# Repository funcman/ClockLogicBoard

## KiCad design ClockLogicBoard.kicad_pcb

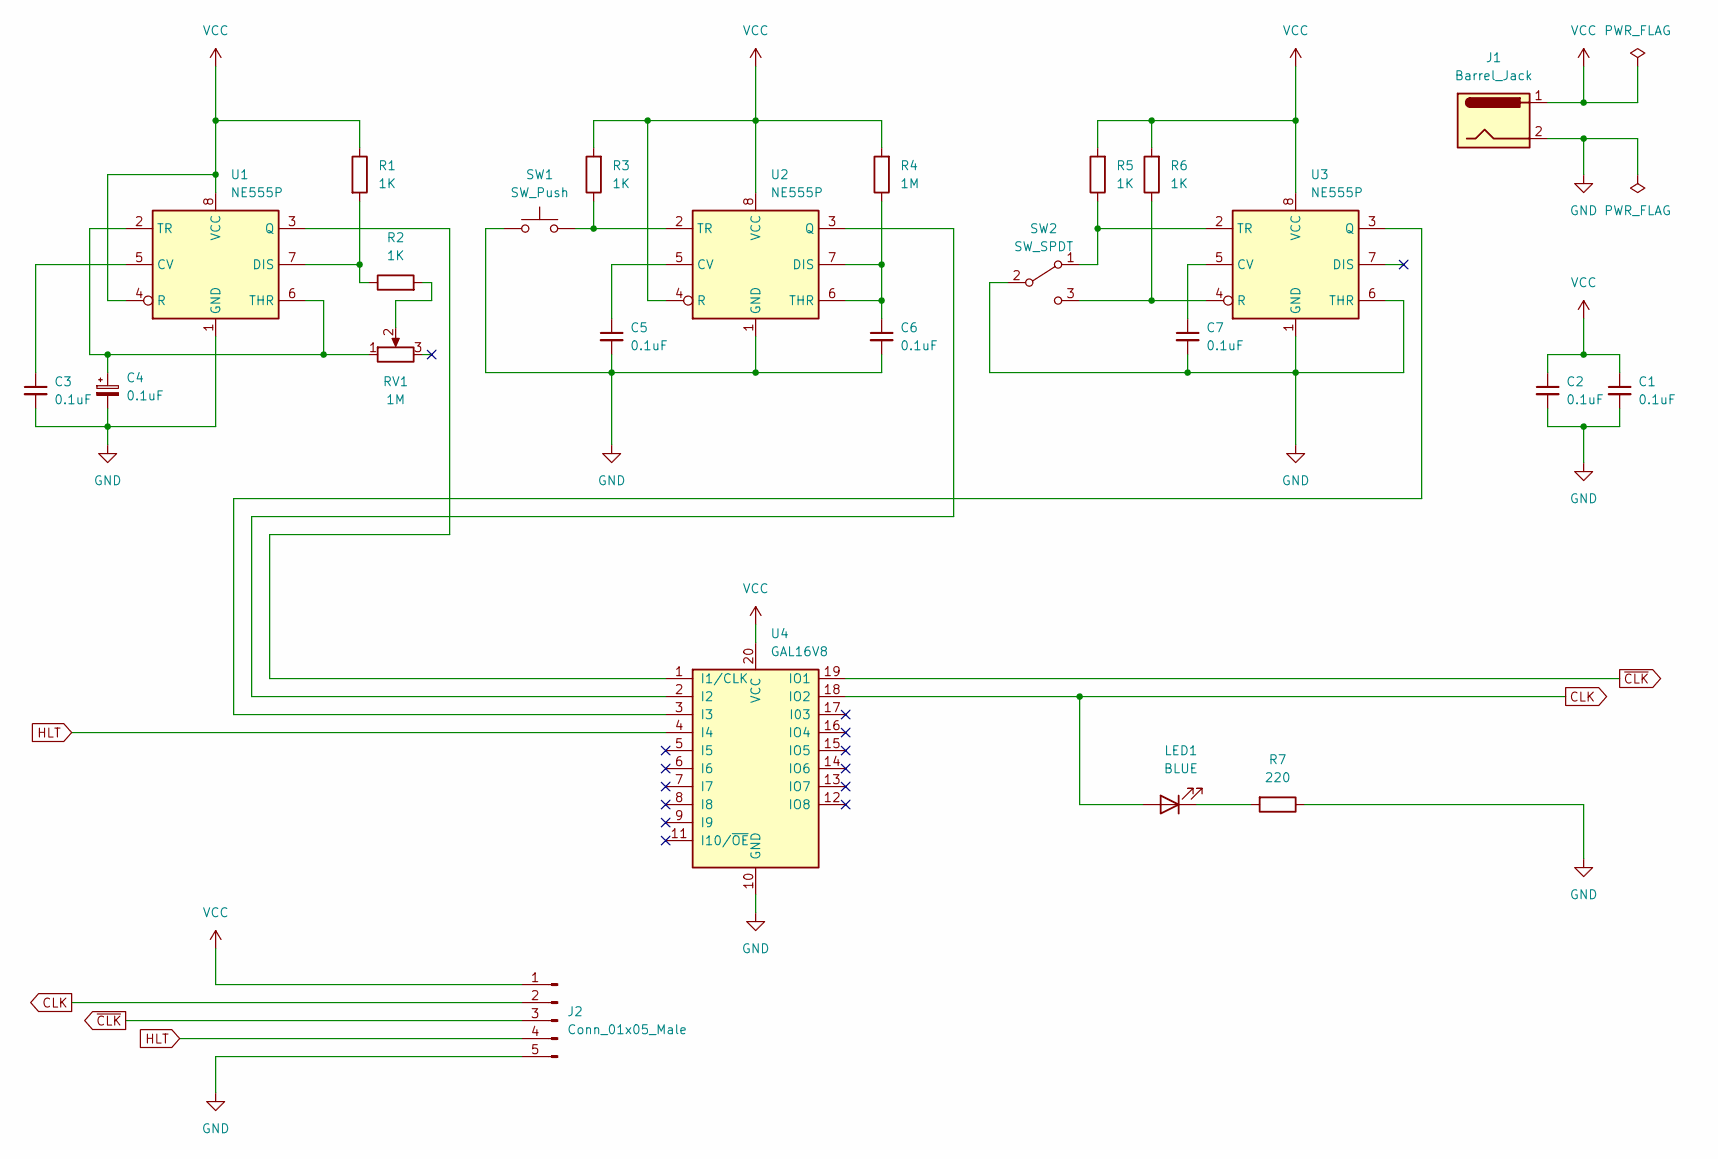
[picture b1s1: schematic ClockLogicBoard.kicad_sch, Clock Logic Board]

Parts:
C1, C2, C3, C5, C6, C7: 0.1uF; C_Disc_D8.0mm_W2.5mm_P5.00mm
C4: 0.1uF; CP_Radial_D4.0mm_P1.50mm
J1: Barrel_Jack; BarrelJack_Horizontal
J2: Conn_01x05_Male; PinHeader_1x05_P2.54mm_Vertical
LED1: BLUE; LED_D5.0mm
R1, R2, R3, R5, R6: 1K; R_Axial_DIN0204_L3.6mm_D1.6mm_P5.08mm_Horizontal
R4: 1M; R_Axial_DIN0204_L3.6mm_D1.6mm_P5.08mm_Horizontal
R7: 220; R_Axial_DIN0204_L3.6mm_D1.6mm_P5.08mm_Horizontal
RV1: 1M; Potentiometer_Bourns_3296W_Vertical
SW1: SW_Push; SW_PUSH_6mm
SW2: SW_SPDT; SW_E-Switch_EG1271_DPDT
U1, U2, U3: NE555P; DIP-8_W7.62mm
U4: GAL16V8; DIP-20_W7.62mm

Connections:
CLK: J2.2, LED1.2 (A), U4.18 (IO2)
GND: C1.2, C2.2, C3.2, C4.2, C5.2, C6.2, C7.2, J1.2, J2.5, R7.1, SW1.1, SW2.2 (B), U1.1 (GND), U2.1 (GND), U3.1 (GND), U3.6 (THR), U4.10 (GND)
HLT: J2.4, U4.4 (I4)
unnamed: C3.1, U1.5 (CV)
unnamed: C4.1, RV1.1, U1.2 (TR), U1.6 (THR)
unnamed: C5.1, U2.5 (CV)
unnamed: C6.1, R4.1, U2.6 (THR), U2.7 (DIS)
unnamed: C7.1, U3.5 (CV)
unnamed: LED1.1 (K), R7.2
unnamed: R1.2, R2.1, U1.7 (DIS)
unnamed: R2.2, RV1.2
unnamed: R3.1, SW1.2, U2.2 (TR)
unnamed: R5.1, SW2.1 (A), U3.2 (TR)
unnamed: R6.1, SW2.3 (C), U3.4 (R)
unnamed: U1.3 (Q), U4.1 (I1/CLK)
unnamed: U2.3 (Q), U4.2 (I2)
unnamed: U3.3 (Q), U4.3 (I3)
VCC: C1.1, C2.1, J1.1, J2.1, R1.1, R3.2, R4.2, R5.2, R6.2, U1.4 (R), U1.8 (VCC), U2.4 (R), U2.8 (VCC), U3.8 (VCC), U4.20 (VCC)
~CLK: J2.3, U4.19 (IO1)

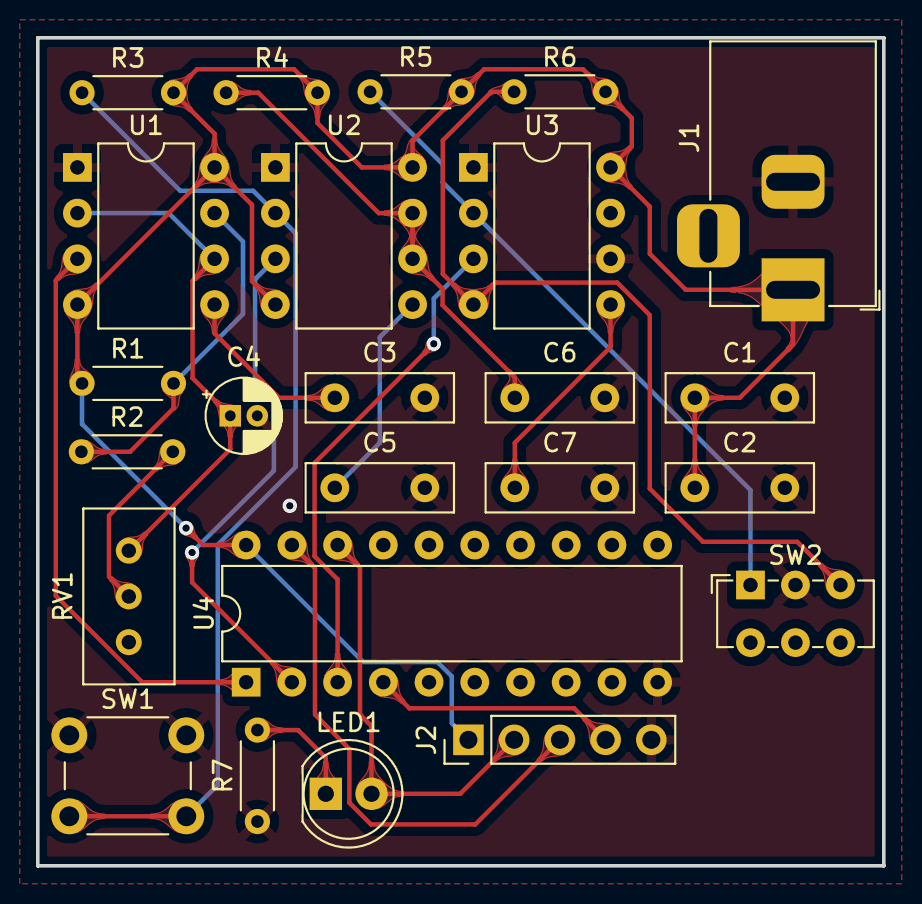
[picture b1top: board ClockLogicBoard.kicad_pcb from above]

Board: 2 copper layers, 47.0 x 46.0 mm, 24 parts (0 on the bottom side), 19 nets.

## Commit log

2023-02-12 prototype
